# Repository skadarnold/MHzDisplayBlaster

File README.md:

# ST-6A Blaster

This is a fork of the MHzDisplayBlaster by Scrap Computing
https://github.com/scrapcomputing/MHzDisplayBlaster

It has been reworked to clone a ST-6A style display board, particularly designed for a Baby AT style case. This case badged as a Gecco was likely the name of the company that built the computer and not the case. This display board is not a perfect match to a ST-6A display, but was the closest I could identify to the style. It will likely need to be modified for your particular case use.

# Assembly Tips
This video shows assembly of the original MHzDisplayBlaster, which is a similar build process.
- Video showing the assembly of rev.0.1 PCB: https://www.youtube.com/watch?v=a4iVehn7APU
 
# Display Configuration
- Each segment of the 7-segment display is configured individually with a jumper
- Each segment corresponds to a pin in the configuration headers
- You can short that pin with one of the neighboring state pins (forming a `T` shape) to set its state, which can be one of the following:
  1. ON when Turbo switch is OFF (jumper to position 1)
  2. ON when Turbo switch is ON (jumper to position 2)
  3. Always ON (jumper to position 3)
  4. Always OFF (no jumper)

# Bill of materials

Gerber files are published in the releases: https://github.com/skadarnold/MHzDisplayBlaster/releases

Reference      | Quantity| Value    | Footprint/Comments
---------------|---------|----------|----------
U1             | 1       |(e.g., LTD-6440G) | 18-DIP (0.600", 15.24mm distance between top and bottom row pins) 2-Digit 7-Segment Display Common Cathode 0.56" Red
J1 J2          | 2       |Conn_02x15| Connector Male PinHeader 2x15 P2.54mm Vertical
J4             | 1       |Conn_01x06| Connector Male PinHeader 1x06 P2.54mm Vertical
R1             | 1       | >= 39 Ohm (100 Ohms recommended)| 3.6 x 1.6mm 1/4 Watt resistor.
R2 R3          | 2       | 330 - 1k Ohm | 3.6 x 1.6mm 1/4 Watt resistor.
U2             | 1       | 74LS04 (	SN7404DR ) | SOIC-14
Jumpers        | 5      |          | 2.54mm pitch jumpers

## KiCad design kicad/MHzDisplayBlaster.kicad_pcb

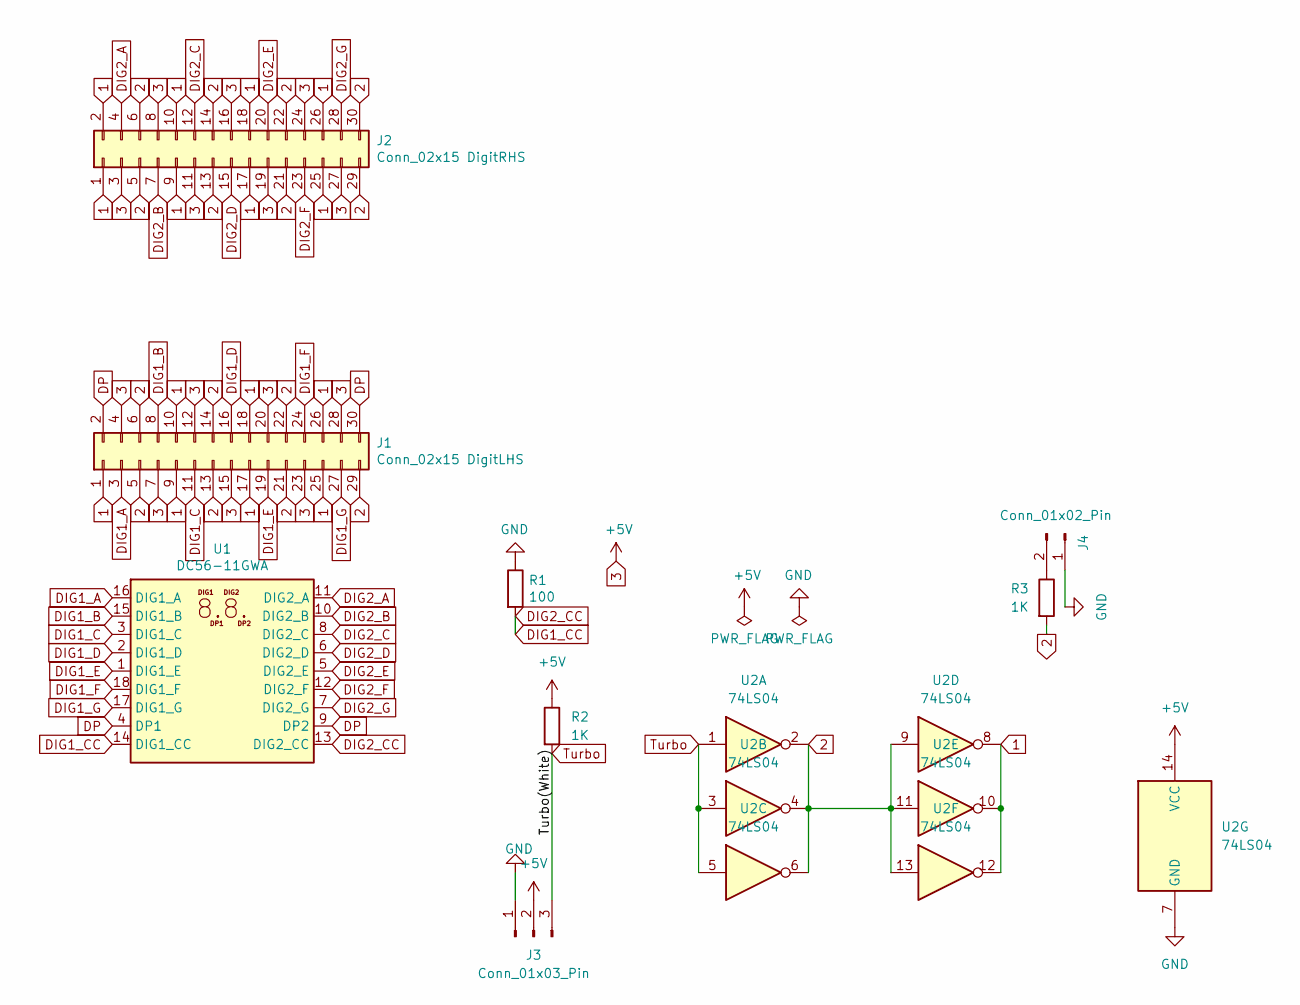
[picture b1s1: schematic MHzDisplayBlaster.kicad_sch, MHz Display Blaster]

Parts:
J1: Conn_02x15 DigitLHS; PinHeader_2x15_P2.54mm_Vertical
J2: Conn_02x15 DigitRHS; PinHeader_2x15_P2.54mm_Vertical
J3: Conn_01x03_Pin; PinHeader_1x03_P2.54mm_Vertical
J4: Conn_01x02_Pin; PinHeader_1x02_P2.54mm_Vertical
R1: 100; R_Axial_DIN0204_L3.6mm_D1.6mm_P5.08mm_Horizontal
R2, R3: 1K; R_Axial_DIN0204_L3.6mm_D1.6mm_P5.08mm_Horizontal
U1: DC56-11GWA; DA56-11CGKWA
U2: 74LS04; SOIC-14_3.9x8.7mm_P1.27mm

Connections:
1: J1.1, J1.9, J1.10, J1.17, J1.18, J1.25, J1.26, J2.1, J2.2, J2.9, J2.10, J2.17, J2.18, J2.25, J2.26, U2.8, U2.10, U2.12
2: J1.5, J1.6, J1.13, J1.14, J1.21, J1.22, J1.29, J2.5, J2.6, J2.13, J2.14, J2.21, J2.22, J2.29, J2.30, R3.2, U2.2, U2.4, U2.6, U2.9, U2.11, U2.13
3: J1.4, J1.7, J1.12, J1.15, J1.20, J1.23, J1.28, J2.3, J2.8, J2.11, J2.16, J2.19, J2.24, J2.27, J3.2, R2.1, U2.14 (VCC)
DIG1_A: J1.3, U1.16 (DIG1_A)
DIG1_B: J1.8, U1.15 (DIG1_B)
DIG1_C: J1.11, U1.3 (DIG1_C)
DIG1_CC: R1.2, U1.13 (DIG2_CC), U1.14 (DIG1_CC)
DIG1_D: J1.16, U1.2 (DIG1_D)
DIG1_E: J1.19, U1.1 (DIG1_E)
DIG1_F: J1.24, U1.18 (DIG1_F)
DIG1_G: J1.27, U1.17 (DIG1_G)
DIG2_A: J2.4, U1.11 (DIG2_A)
DIG2_B: J2.7, U1.10 (DIG2_B)
DIG2_C: J2.12, U1.8 (DIG2_C)
DIG2_D: J2.15, U1.6 (DIG2_D)
DIG2_E: J2.20, U1.5 (DIG2_E)
DIG2_F: J2.23, U1.12 (DIG2_F)
DIG2_G: J2.28, U1.7 (DIG2_G)
DP: J1.2, J1.30, U1.4 (DP1), U1.9 (DP2)
GND: J3.1, J4.1, R1.1, U2.7 (GND)
unnamed: J4.2, R3.1
Turbo: J3.3, R2.2, U2.1, U2.3, U2.5

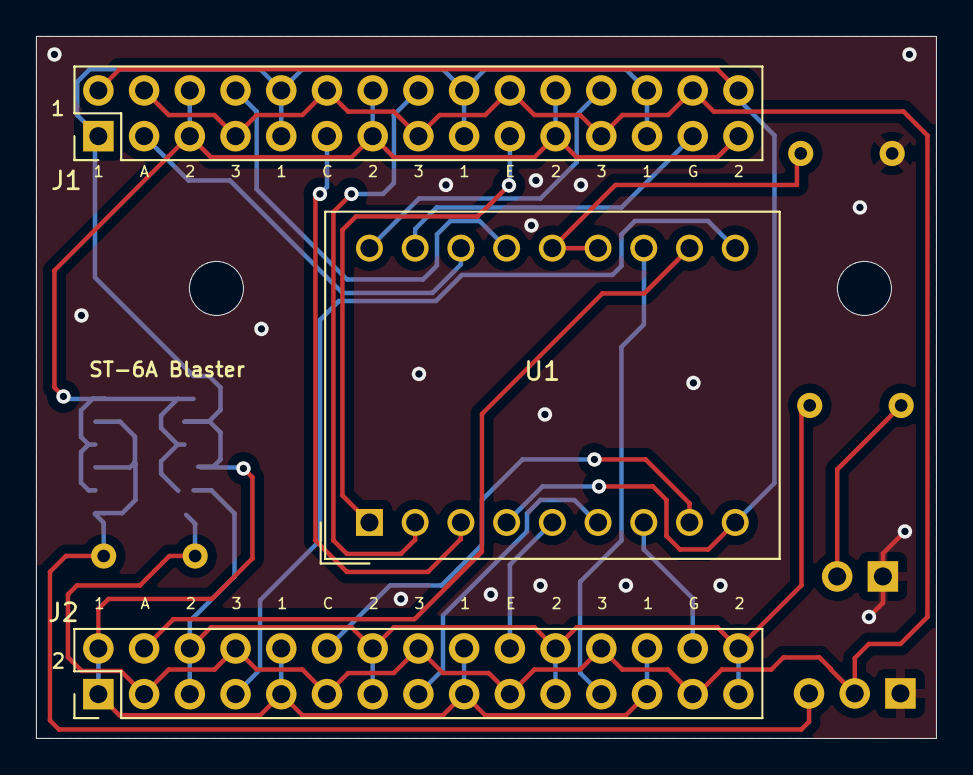
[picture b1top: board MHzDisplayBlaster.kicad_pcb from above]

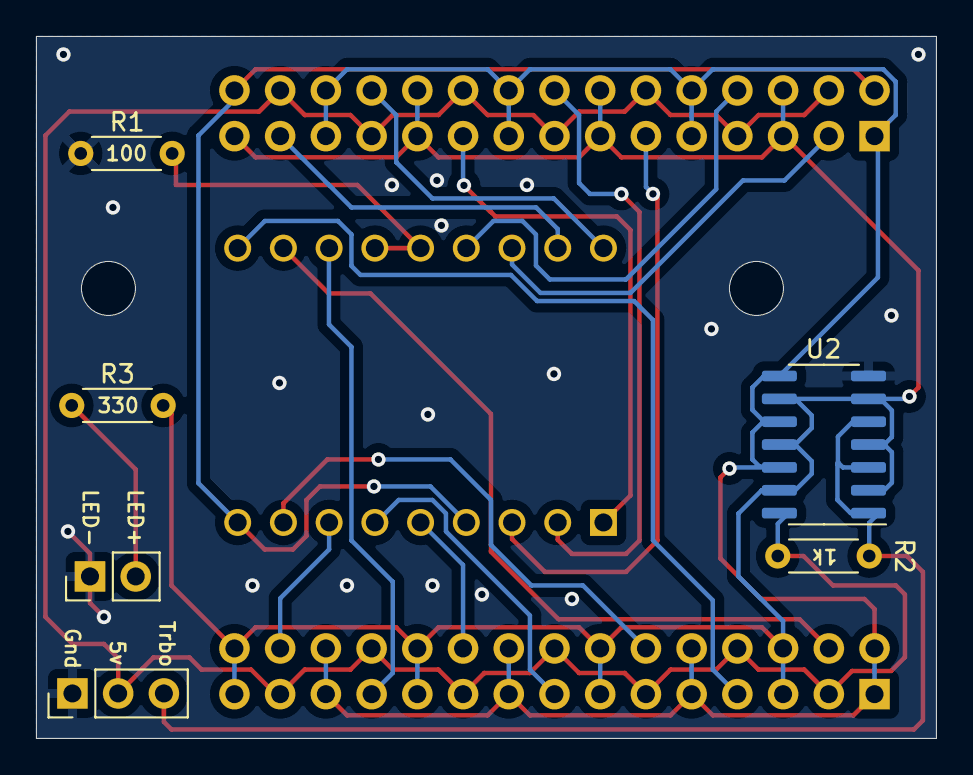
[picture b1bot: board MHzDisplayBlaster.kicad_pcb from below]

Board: 2 copper layers, 50.0 x 39.0 mm, 9 parts (6 on the bottom side), 22 nets.

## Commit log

2024-09-13 Initial Redesign
    Layout rearranged for Gecco labeled Baby AT case. Not even ready as a beta release.
2024-09-15 Split 7-pin connector
2024-09-15 PCB Arrange
2024-09-15 Not sure why not in last
2024-09-15 Update Schematic 74LS04
2024-10-11 Cleanup and Routing
2024-10-11 Small cleanup to text
2024-10-11 Remove ground plane
2024-10-13 Major Refactor and Cleanup
2024-10-13 Remove Rule Zones and extend trace for screw clearance
2024-10-13 Move R2 to Back
2024-10-13 Move J3 Silk to Back
2024-10-13 Add vias to fill in ground planes
2024-10-13 Raise J3 to higher position
2024-10-13 Adjust via position for J1 text
2024-10-13 Fix missing routes on 7404
2024-10-13 More trace cleanup
2024-10-16 Add Graphical Notes
2024-10-17 Connect Display pin 4 & Trace Cleanup
2024-10-17 Refill ground planes
2024-10-17 Add Turbo LED Header
2024-10-17 Adjust ground plane vias
2024-11-18 Change HEX Inverter position, clean up layout
2024-11-18 Slight adjustment to display and mounting holes
2024-11-18 Rotate HEX inverter, finalize
2024-12-03 Updated Changes / Mostly unknown - probably zone fills
